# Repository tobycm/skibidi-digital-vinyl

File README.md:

# skibidi-digital-vinyl

a really cool vinyl emulator with digital tech

## Idea

Discs are made out of CH32V003 mcu, BY25Q32 flash, acts as a storage for audio file. Powered through pogo pins when placed in the player.

The player is powered with a RP2040 mcu, PTC PT8211-S DAC, and PAM8403 amplifier. USB powered, maybe battery powered in the future.

Maybe add a spinning motor in the future for extra effect.

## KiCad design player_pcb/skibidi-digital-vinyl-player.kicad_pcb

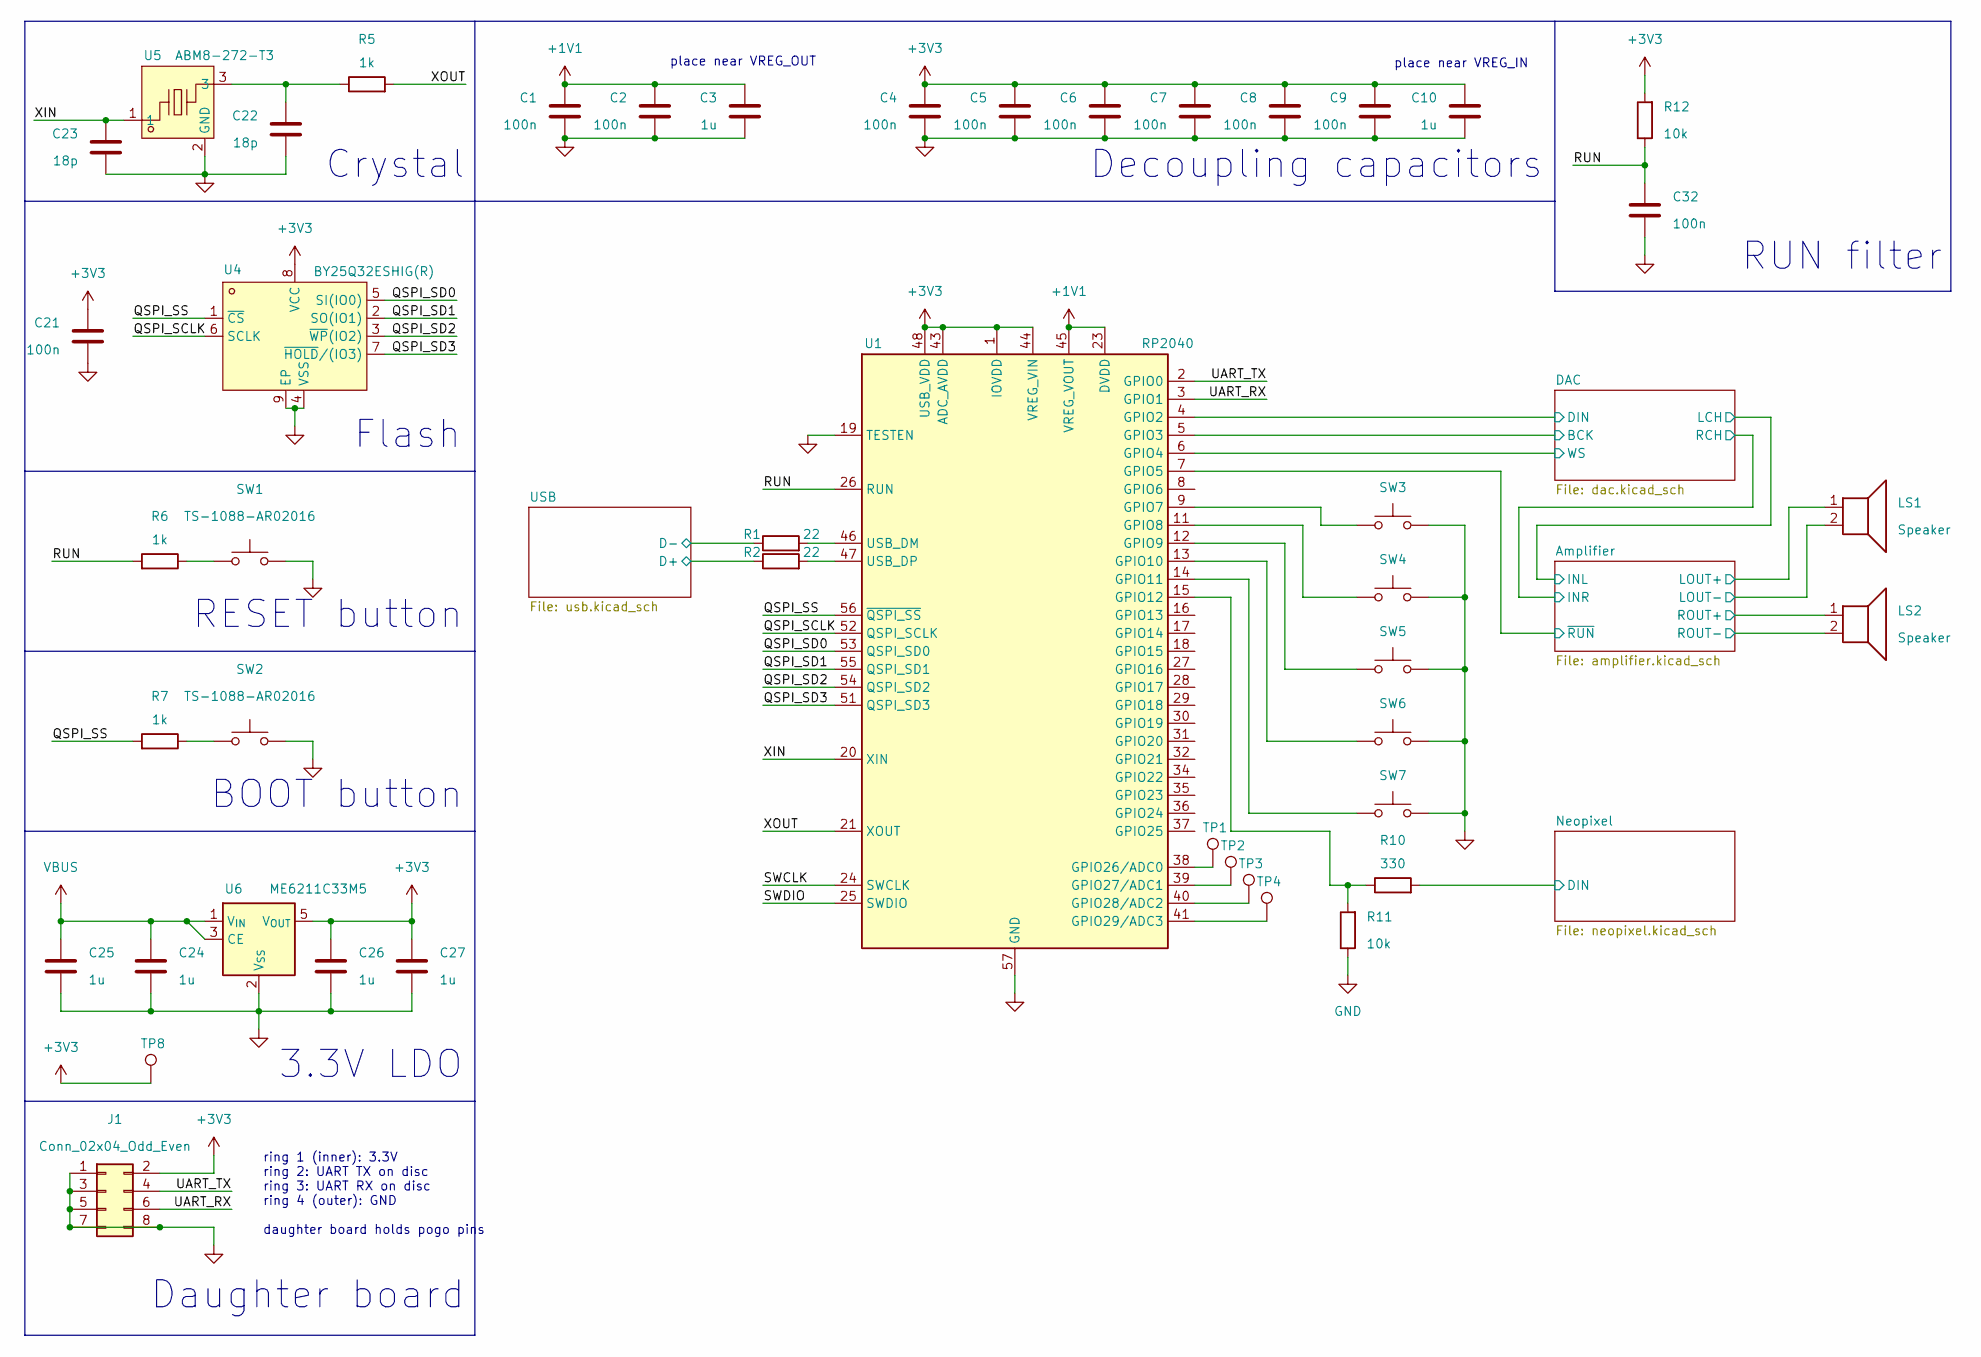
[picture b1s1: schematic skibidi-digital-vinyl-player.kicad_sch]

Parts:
C1, C2, C4, C5, C6, C7, C8, C9, C21, C32: 100n; C_0402_1005Metric; LCSC Part # C1525
C3, C10, C24, C25, C26, C27: 1u; C_0402_1005Metric; LCSC Part # C52923
C22, C23: 18p; C_0402_1005Metric; LCSC Part # C1549
J1: Conn_02x04_Odd_Even; JST_XH_S8B-XH-A_1x08_P2.50mm_Horizontal
LS1, LS2: Speaker; PinSocket_1x02_P2.54mm_Vertical
R1, R2: 22; R_0402_1005Metric; LCSC Part # C25092
R5, R6, R7: 1k; R_0603_1608Metric; LCSC Part # C21190
R10: 330; R_0603_1608Metric; LCSC Part # C23138
R11, R12: 10k; R_0603_1608Metric; LCSC Part # C25804
SW1, SW2: TS-1088-AR02016; SW_SPST_TS-1088-xR020; LCSC Part # C720477
SW3, SW4, SW5, SW6, SW7: SW_Push; SW_MX_1u
TP1, TP2, TP3, TP4, TP8: TestPoint; TestPoint_Pad_D1.0mm
U1: RP2040; QFN-56-1EP_7x7mm_P0.4mm_EP3.2x3.2mm; LCSC Part # C2040
U4: BY25Q32ESHIG(R); DFN-8_L4.0-W3.0-P0.80-TL-EP_GT5YL24A1Y520; LCSC Part C50176326
U5: ABM8-272-T3; CRYSTAL-SMD_4P-L3.2-W2.5-BL; LCSC Part C20625731
U6: ME6211C33M5; SOT-23-5

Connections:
+1V1: C1.1, C2.1, C3.1, U1.23 (DVDD), U1.45 (VREG_VOUT), U1.50 (DVDD)
+3V3: C4.1, C5.1, C6.1, C7.1, C8.1, C9.1, C10.1, C21.1, C26.1, C27.1, J1.2, R12.2, TP8.1, U1.1 (IOVDD), U1.10 (IOVDD), U1.22 (IOVDD), U1.33 (IOVDD), U1.42 (IOVDD), U1.43 (ADC_AVDD), U1.44 (VREG_VIN), U1.48 (USB_VDD), U1.49 (IOVDD), U4.8 (VCC), U6.5 (V_{OUT})
/Amplifier/LOUT+: LS1.1; also elsewhere on the board
/Amplifier/LOUT-: LS1.2; also elsewhere on the board
/Amplifier/ROUT+: LS2.1; also elsewhere on the board
/Amplifier/ROUT-: LS2.2; also elsewhere on the board
/Amplifier/~RUN: U1.7 (GPIO5); also elsewhere on the board
/DAC/BCK: U1.5 (GPIO3); also elsewhere on the board
/DAC/DIN: U1.4 (GPIO2); also elsewhere on the board
/DAC/WS: U1.6 (GPIO4); also elsewhere on the board
/Neopixel/DIN: R10.2; also elsewhere on the board
/QSPI_SCLK: U1.52 (QSPI_SCLK), U4.6 (SCLK)
/QSPI_SD0: U1.53 (QSPI_SD0), U4.5 (SI(IO0))
/QSPI_SD1: U1.55 (QSPI_SD1), U4.2 (SO(IO1))
/QSPI_SD2: U1.54 (QSPI_SD2), U4.3 (~WP(IO2))
/QSPI_SD3: U1.51 (QSPI_SD3), U4.7 (~HOLD/(IO3))
/RUN: C32.1, R6.2, R12.1, U1.26 (RUN)
/SWCLK: U1.24 (SWCLK)
/SWDIO: U1.25 (SWDIO)
/UART_RX: J1.6, U1.3 (GPIO1)
/UART_TX: J1.4, U1.2 (GPIO0)
/USB/D+: R2.1; also elsewhere on the board
/USB/D-: R1.1; also elsewhere on the board
/XIN: C23.1, U1.20 (XIN), U5.1
/XOUT: R5.2, U1.21 (XOUT)
unnamed: C22.1, R5.1, U5.3
unnamed: R6.1, SW1.2
unnamed: SW3.1, U1.9 (GPIO7)
unnamed: SW4.1, U1.11 (GPIO8)
unnamed: SW5.1, U1.12 (GPIO9)
unnamed: SW6.1, U1.13 (GPIO10)
unnamed: SW7.1, U1.14 (GPIO11)
unnamed: R10.1, R11.2, U1.15 (GPIO12)
unnamed: TP1.1, U1.38 (GPIO26/ADC0)
unnamed: TP2.1, U1.39 (GPIO27/ADC1)
unnamed: TP3.1, U1.40 (GPIO28/ADC2)
unnamed: TP4.1, U1.41 (GPIO29/ADC3)
unnamed: R1.2, U1.46 (USB_DM)
unnamed: R2.2, U1.47 (USB_DP)
VBUS: C24.1, C25.1, U6.1 (V_{IN}), U6.3 (CE); also elsewhere on the board

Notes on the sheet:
ring 1 (inner): 3.3V ring 2: UART TX on disc ring 3: UART RX on disc ring 4 (outer): GND daughter board holds pogo pins
place near VREG_IN
Flash
BOOT button
3.3V LDO
RUN filter
RESET button
Decoupling capacitors
Daughter board
Crystal
place near VREG_OUT

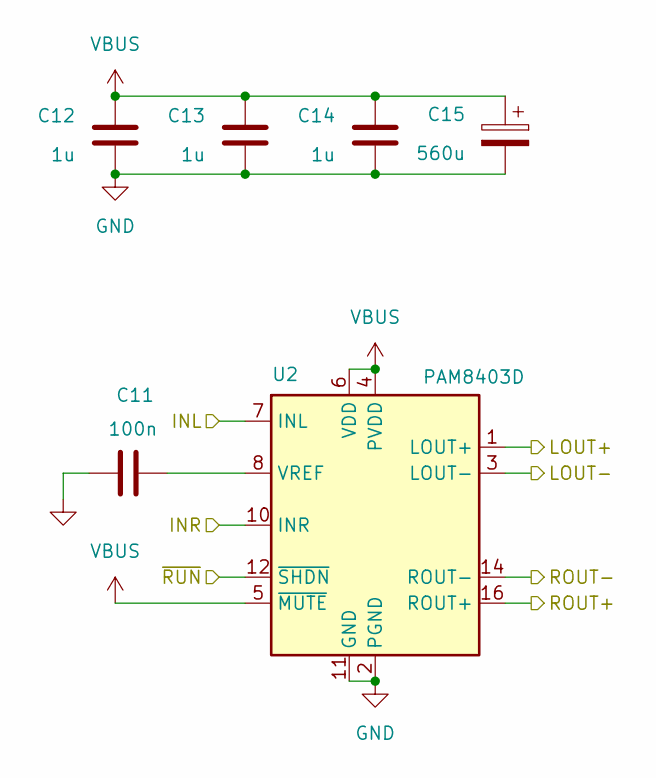
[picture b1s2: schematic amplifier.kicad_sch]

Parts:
C11: 100n; C_0402_1005Metric; LCSC Part # C1525
C12, C13, C14: 1u; C_0402_1005Metric; LCSC Part # C52923
C15: 560u; CP_Elec_10x10; LCSC Part # C19673857
U2: PAM8403D; SOIC-16_3.9x9.9mm_P1.27mm; LCSC Part # C53055751

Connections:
/Amplifier/INL: U2.7 (INL); also elsewhere on the board
/Amplifier/INR: U2.10 (INR); also elsewhere on the board
/Amplifier/LOUT+: U2.1 (LOUT+); also elsewhere on the board
/Amplifier/LOUT-: U2.3 (LOUT-); also elsewhere on the board
/Amplifier/ROUT+: U2.16 (ROUT+); also elsewhere on the board
/Amplifier/ROUT-: U2.14 (ROUT-); also elsewhere on the board
/Amplifier/~RUN: U2.12 (~SHDN); also elsewhere on the board
unnamed: C11.1, U2.8 (VREF)
VBUS: C12.1, C13.1, C14.1, C15.1, U2.4 (PVDD), U2.5 (~MUTE), U2.6 (VDD), U2.13 (PVDD); also elsewhere on the board

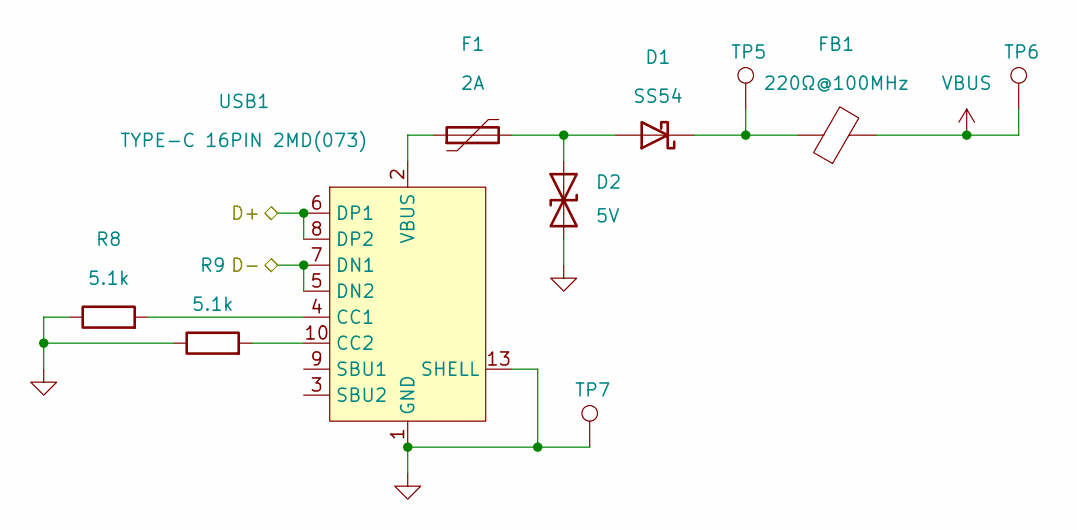
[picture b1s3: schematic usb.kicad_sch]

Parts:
D1: SS54; D_SMA; LCSC Part # C22452
D2: 5V; D_SOD-523; LCSC Part # C82044
F1: 2A; Fuse_1206_3216Metric; LCSC Part # C883135
FB1: 220Ω@100MHz; R_0805_2012Metric_Pad1.20x1.40mm_HandSolder; LCSC Part # C85840
R8, R9: 5.1k; R_0603_1608Metric; LCSC Part # C23186
TP5, TP6, TP7: TestPoint; TestPoint_Pad_D1.0mm
USB1: TYPE-C 16PIN 2MD(073); USB-C-SMD_TYPE-C-6PIN-2MD-073; LCSC Part C2765186

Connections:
/USB/D+: USB1.6 (DP1), USB1.8 (DP2); also elsewhere on the board
/USB/D-: USB1.5 (DN2), USB1.7 (DN1); also elsewhere on the board
unnamed: D1.2 (A), D2.1 (A1), F1.2
unnamed: D1.1 (K), FB1.1, TP5.1
unnamed: F1.1, USB1.2 (VBUS), USB1.11 (VBUS)
unnamed: R8.2, USB1.4 (CC1)
unnamed: R9.2, USB1.10 (CC2)
VBUS: FB1.2, TP6.1; also elsewhere on the board

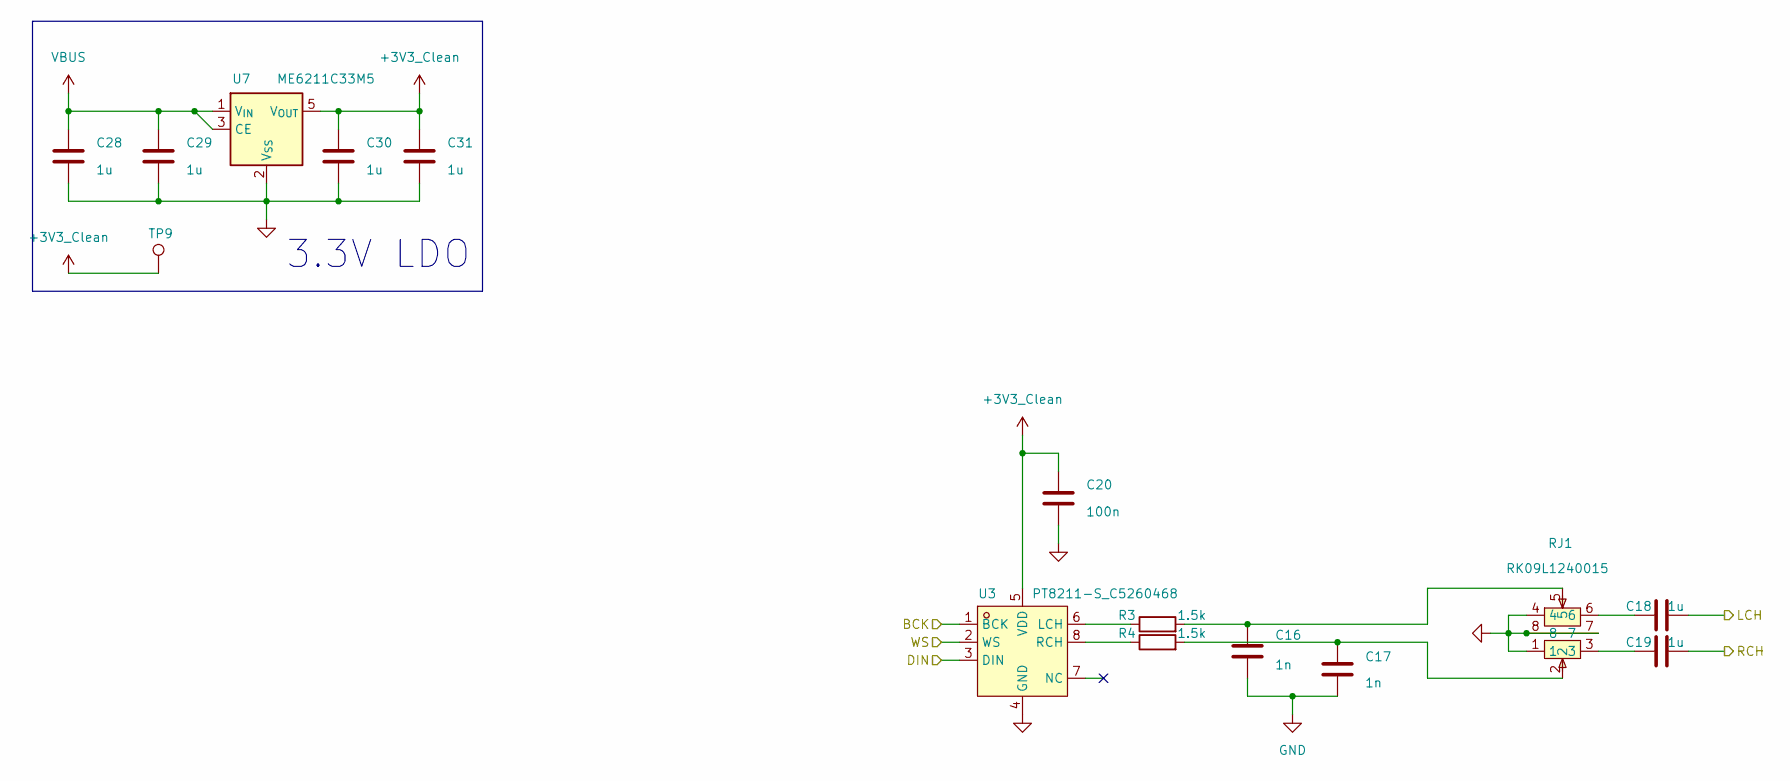
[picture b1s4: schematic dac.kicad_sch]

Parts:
C16, C17: 1n; C_0402_1005Metric; LCSC Part # C52923
C18, C19, C28, C29, C30, C31: 1u; C_0402_1005Metric; LCSC Part # C52923
C20: 100n; C_0402_1005Metric; LCSC Part # C1525
R3, R4: 1.5k; R_0402_1005Metric; LCSC Part # C25867
RJ1: RK09L1240015; RES-ADJ-TH_RK09L1240A12; LCSC Part C7471751
TP9: TestPoint; TestPoint_Pad_D1.0mm
U3: PT8211-S_C5260468; SOIC-8_L4.9-W3.9-P1.27-LS6.0-BL; LCSC Part C5260468
U7: ME6211C33M5; SOT-23-5

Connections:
+3V3_Clean: C20.1, C30.1, C31.1, TP9.1, U3.5 (VDD), U7.5 (V_{OUT})
/Amplifier/INL: C18.2; also elsewhere on the board
/Amplifier/INR: C19.2; also elsewhere on the board
/DAC/BCK: U3.1 (BCK); also elsewhere on the board
/DAC/DIN: U3.3 (DIN); also elsewhere on the board
/DAC/WS: U3.2 (WS); also elsewhere on the board
unnamed: C16.2, R3.2, RJ1.5
unnamed: C17.2, R4.2, RJ1.2
unnamed: C18.1, RJ1.6
unnamed: C19.1, RJ1.3
unnamed: R3.1, U3.6 (LCH)
unnamed: R4.1, U3.8 (RCH)
VBUS: C28.1, C29.1, U7.1 (V_{IN}), U7.3 (CE); also elsewhere on the board

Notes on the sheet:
3.3V LDO

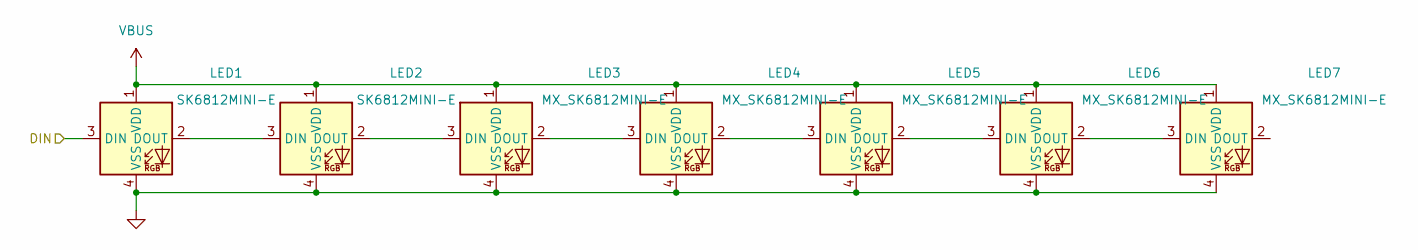
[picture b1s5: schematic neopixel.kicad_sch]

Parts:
LED1, LED2: SK6812MINI-E; LED_6028R
LED3, LED4, LED5, LED6, LED7: MX_SK6812MINI-E; LED_MX_6028R

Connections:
/Neopixel/DIN: LED1.3 (DIN); also elsewhere on the board
unnamed: LED1.2 (DOUT), LED2.3 (DIN)
unnamed: LED2.2 (DOUT), LED3.3 (DIN)
unnamed: LED3.2 (DOUT), LED4.3 (DIN)
unnamed: LED4.2 (DOUT), LED5.3 (DIN)
unnamed: LED5.2 (DOUT), LED6.3 (DIN)
unnamed: LED6.2 (DOUT), LED7.3 (DIN)
VBUS: LED1.1 (VDD), LED2.1 (VDD), LED3.1 (VDD), LED4.1 (VDD), LED5.1 (VDD), LED6.1 (VDD), LED7.1 (VDD); also elsewhere on the board

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
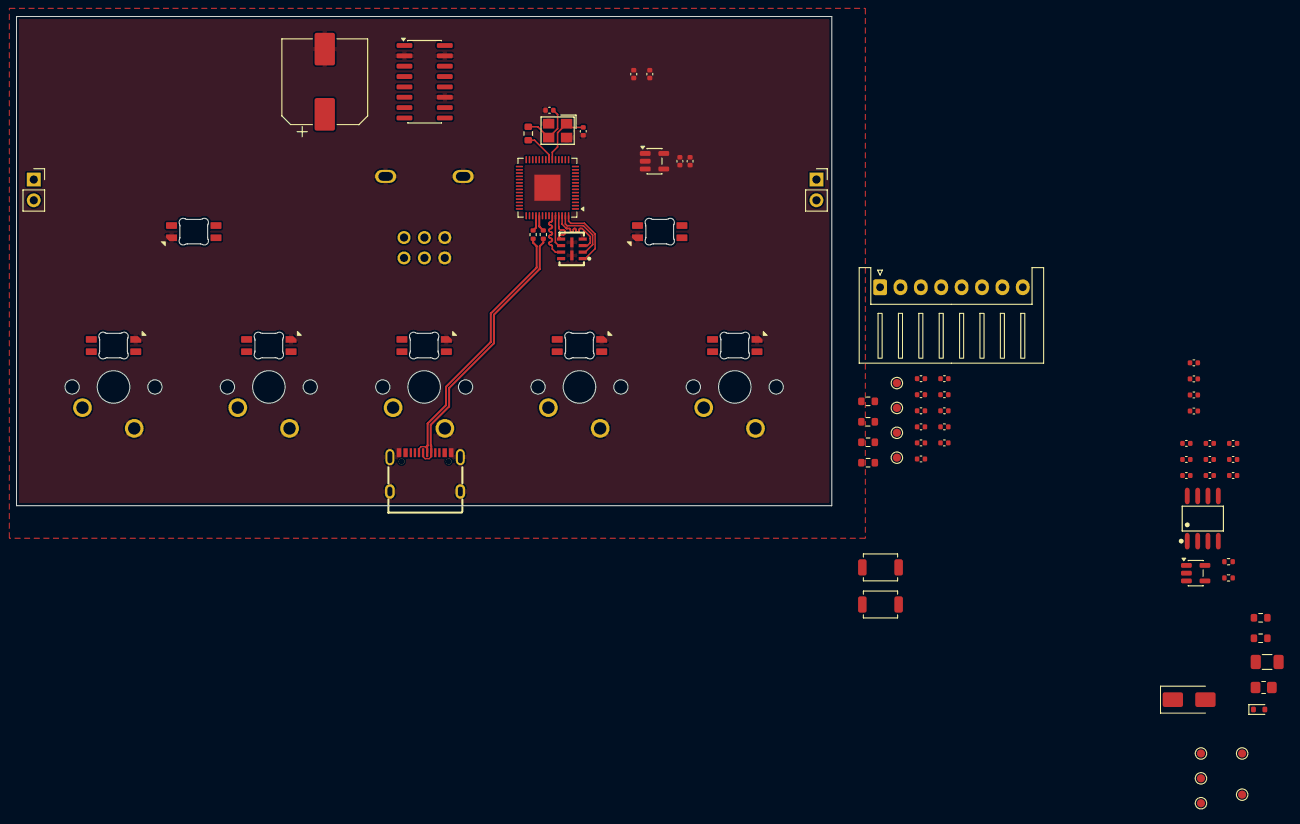
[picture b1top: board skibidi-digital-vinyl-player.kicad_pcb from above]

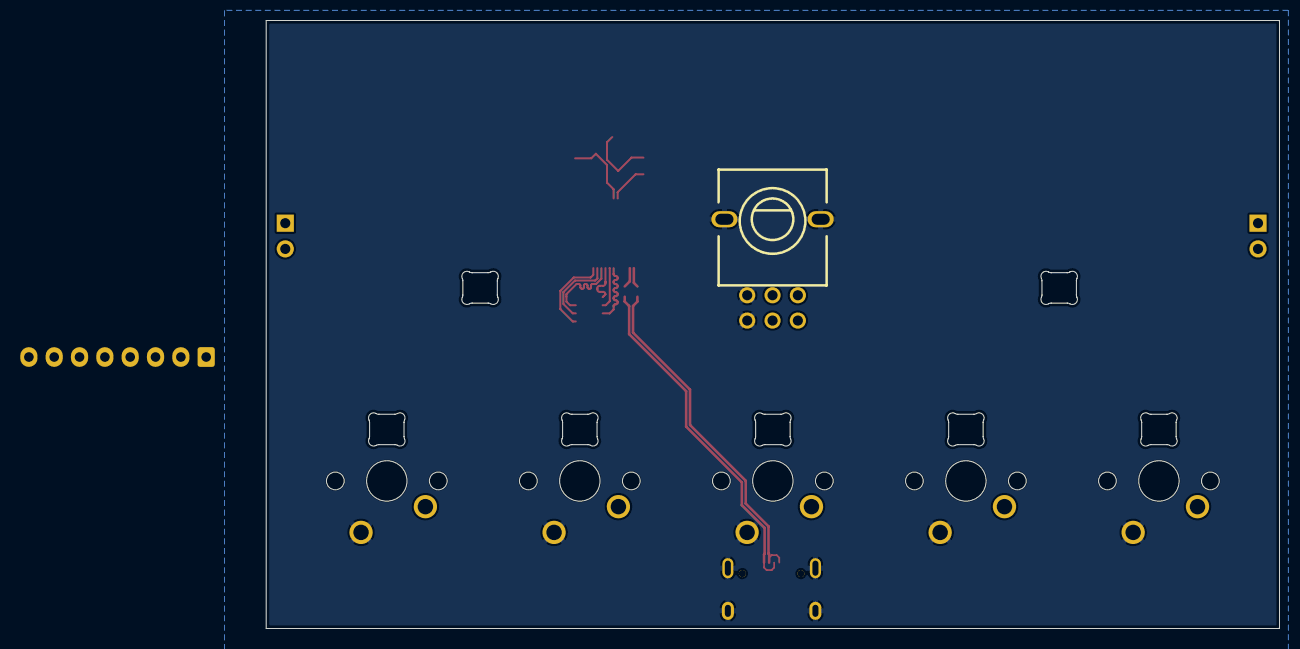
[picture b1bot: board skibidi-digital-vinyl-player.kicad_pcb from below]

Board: 2 copper layers, 100.0 x 60.0 mm, 81 parts (6 on the bottom side), 62 nets.

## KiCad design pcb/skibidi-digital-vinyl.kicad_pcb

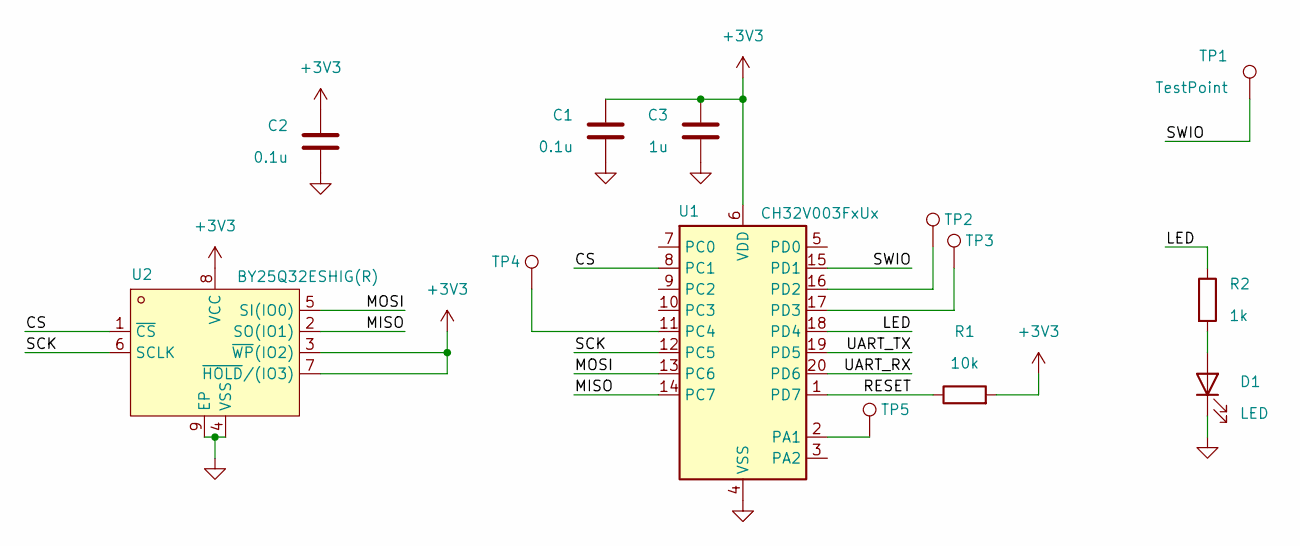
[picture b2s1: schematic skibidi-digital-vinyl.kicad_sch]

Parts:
C1, C2: 0.1u; C_0402_1005Metric; LCSC Part # C1525
C3: 1u; C_0402_1005Metric; LCSC Part # C52923
D1: LED; LED_0603_1608Metric; LCSC Part # C22371297
R1: 10k; R_0603_1608Metric; LCSC Part # C25804
R2: 1k; R_0603_1608Metric; LCSC Part # C21190
TP1, TP2, TP3, TP4, TP5: TestPoint; TestPoint_Pad_D1.0mm
U1: CH32V003FxUx; QFN-20-1EP_3x3mm_P0.4mm_EP1.65x1.65mm
U2: BY25Q32ESHIG(R); DFN-8_L4.0-W3.0-P0.80-TL-EP_GT5YL24A1Y520; LCSC Part C50176326

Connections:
+3V3: C1.1, C2.1, C3.1, R1.2, U1.6 (VDD), U2.3 (~WP(IO2)), U2.7 (~HOLD/(IO3)), U2.8 (VCC)
/CS: U1.8 (PC1), U2.1 (~CS)
/LED: R2.1, U1.18 (PD4)
/MISO: U1.14 (PC7), U2.2 (SO(IO1))
/MOSI: U1.13 (PC6), U2.5 (SI(IO0))
/RESET: R1.1, U1.1 (PD7)
/SCK: U1.12 (PC5), U2.6 (SCLK)
/SWIO: TP1.1, U1.15 (PD1)
/UART_RX: U1.20 (PD6)
/UART_TX: U1.19 (PD5)
GND: C1.2, C2.2, C3.2, D1.1 (K), U1.4 (VSS), U1.21 (VSS), U2.4 (VSS), U2.9 (EP), U2.10 (EP)
unnamed: D1.2 (A), R2.2
unnamed: TP5.1, U1.2 (PA1)
unnamed: TP4.1, U1.11 (PC4)
unnamed: TP2.1, U1.16 (PD2)
unnamed: TP3.1, U1.17 (PD3)

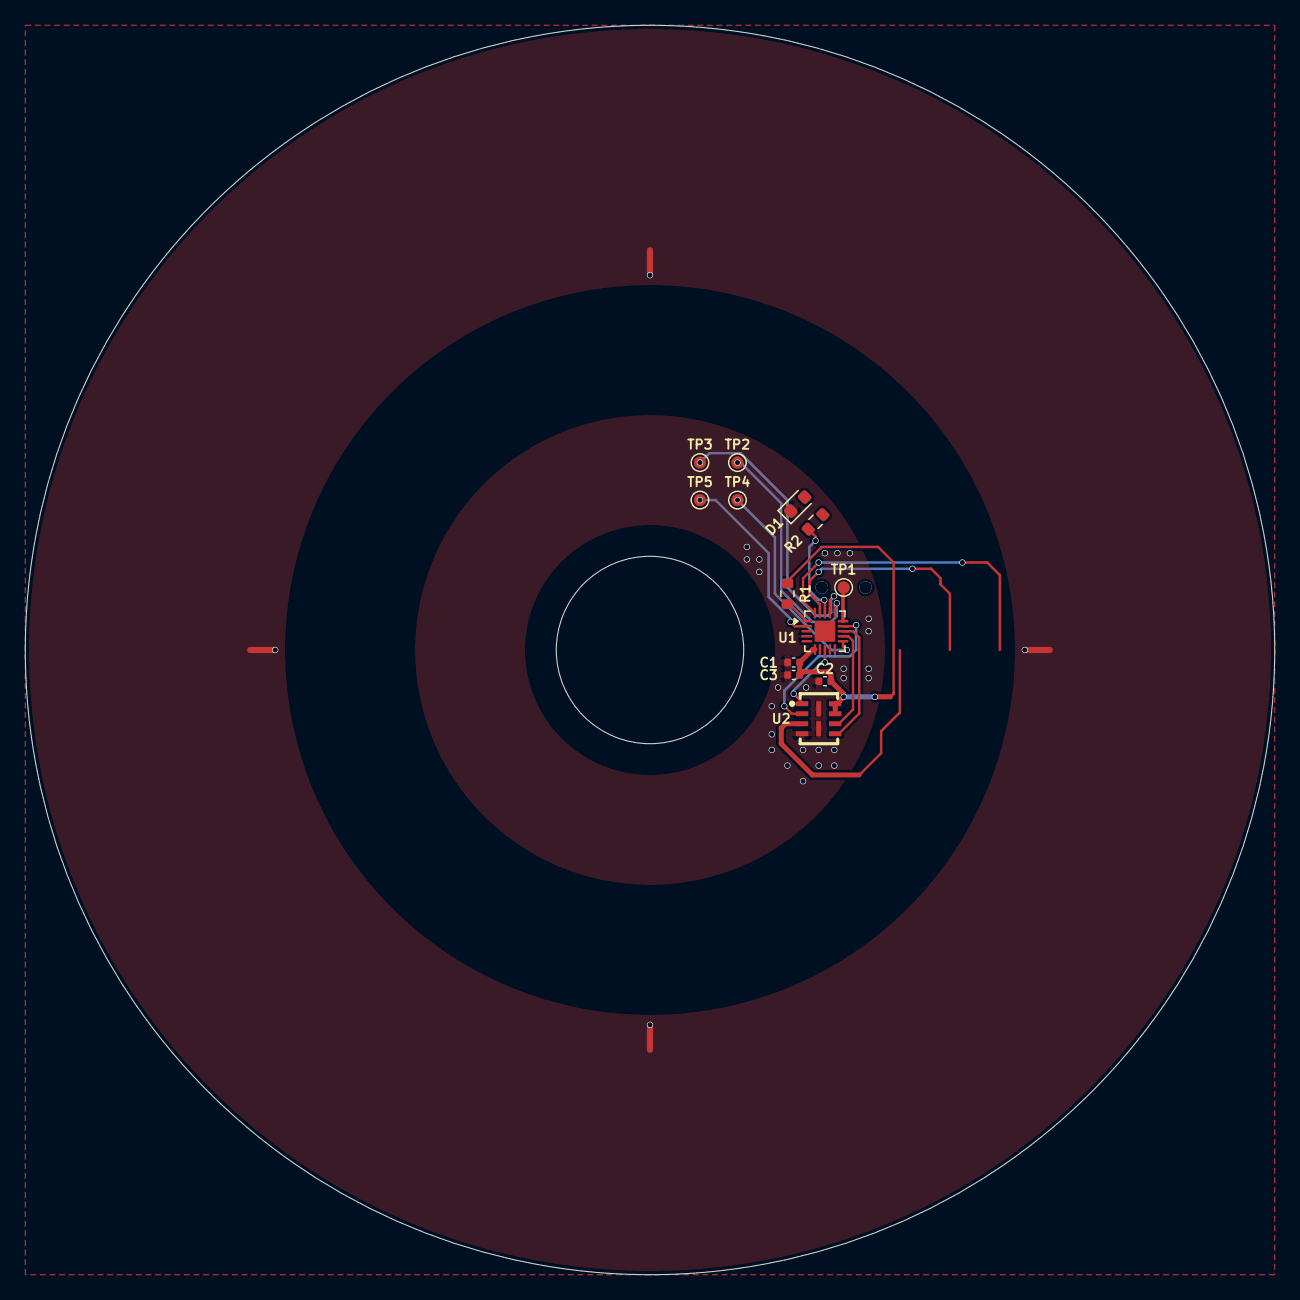
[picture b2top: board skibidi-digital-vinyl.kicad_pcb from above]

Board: 2 copper layers, 100.0 x 100.0 mm, 13 parts (0 on the bottom side), 14 nets.

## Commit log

2026-01-31 general parts researched
2026-02-01 finished disc schematic, might add testpoints later to make full use of the ch32v003
2026-02-01 disc routing done
2026-02-01 update silkscreen text
2026-02-01 move to different folder
2026-02-01 most wiring done, only intracommunication with different modules wiring left
2026-02-01 second to done
